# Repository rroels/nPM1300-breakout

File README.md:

# Nordic nPM1300 Breakout Board

> [!WARNING]
> The information and material (code, designs, files, ...) are provided "AS IS". We make no representation or warranty of any kind, express or implied, regarding the accuracy, adequacy, validity, reliability, availability, or completeness of any information or material. Use this at your own risk.

> [!WARNING]
> At the time of writing this PCB has not even been produced yet, and as such, it has not even been tested yet! Once it has been properly tested, I will confirm that everything works as expected.

## Introduction

This is a breakout board for the Nordic nPM1300 Power Management IC.

[https://www.nordicsemi.com/Products/nPM1300](https://www.nordicsemi.com/Products/nPM1300)

## Change Log

* v1.0
  * Initial design 

## Design Considerations

In this design, the nPM1300 is configured like this:

* BUCK1 disabled
* BUCK2 enabled, for converting battery or USB input to 3.3V
* 2 load switches at 3.3V (LS1 and LS2)
* no LDO 
* 3 LEDs
* I2C interface

## Schematics 

## How to Obtain the Physical PCB

The Gerber file is in this repository (`kicad/gerbers/nPM1300-breakout.zip`). Simply upload this file a PCB manufacturer of your choice (JLPCB, PCBWay, ...), and you they will make it for you for as low as \$5 for 5 pieces (with the cheapest shipping option, which can take a few weeks).

For JLCPCB, select the order number option where they will replace "JLCJLCJLCJLC" on the board with the actual order number.

> [!WARNING]
> Note that will still have to solder the components onto the PCB yourself!

## How to Edit Design

Everything you need to edit this design in KiCad 8 is included in the repository.

However, this project uses symbols, footprints and 3D models from [Component Search Engine](https://componentsearchengine.com/). Their license allows us to do pretty much whatever we want with them, except redistributing them. For this reason I can't include them in this repository.

If you would like to edit the design yourself, you will need to download the following component libraries from [https://componentsearchengine.com/](https://componentsearchengine.com/) (it's free!):

* [https://componentsearchengine.com/part-view/NPM1300-QEAA-R/Nordic%20Semiconductor](https://componentsearchengine.com/part-view/NPM1300-QEAA-R/Nordic%20Semiconductor)
* [https://componentsearchengine.com/part-view/53261-0271/Molex](https://componentsearchengine.com/part-view/53261-0271/Molex)

You will also need this from SnapEDA:

* [https://www.snapeda.com/parts/21296912/TE%20Connectivity/view-part/?ref=te_in&t=USB4105-GF-A&con_ref=None](https://www.snapeda.com/parts/21296912/TE%20Connectivity/view-part/?ref=te_in&t=USB4105-GF-A&con_ref=None)

From the downloaded zip files, move the content of the `KiCad` and `3D` subfolders into the project structure, so that the end-result looks like this:

The KiCad project is configured to look for these files in these locations, using relative paths, so no changes to the project itself are required.	

## Sources

* [https://www.nordicsemi.com/Products/nPM1300](https://www.nordicsemi.com/Products/nPM1300)
* [https://docs.nordicsemi.com/category/npm1300-category](https://docs.nordicsemi.com/category/npm1300-category)

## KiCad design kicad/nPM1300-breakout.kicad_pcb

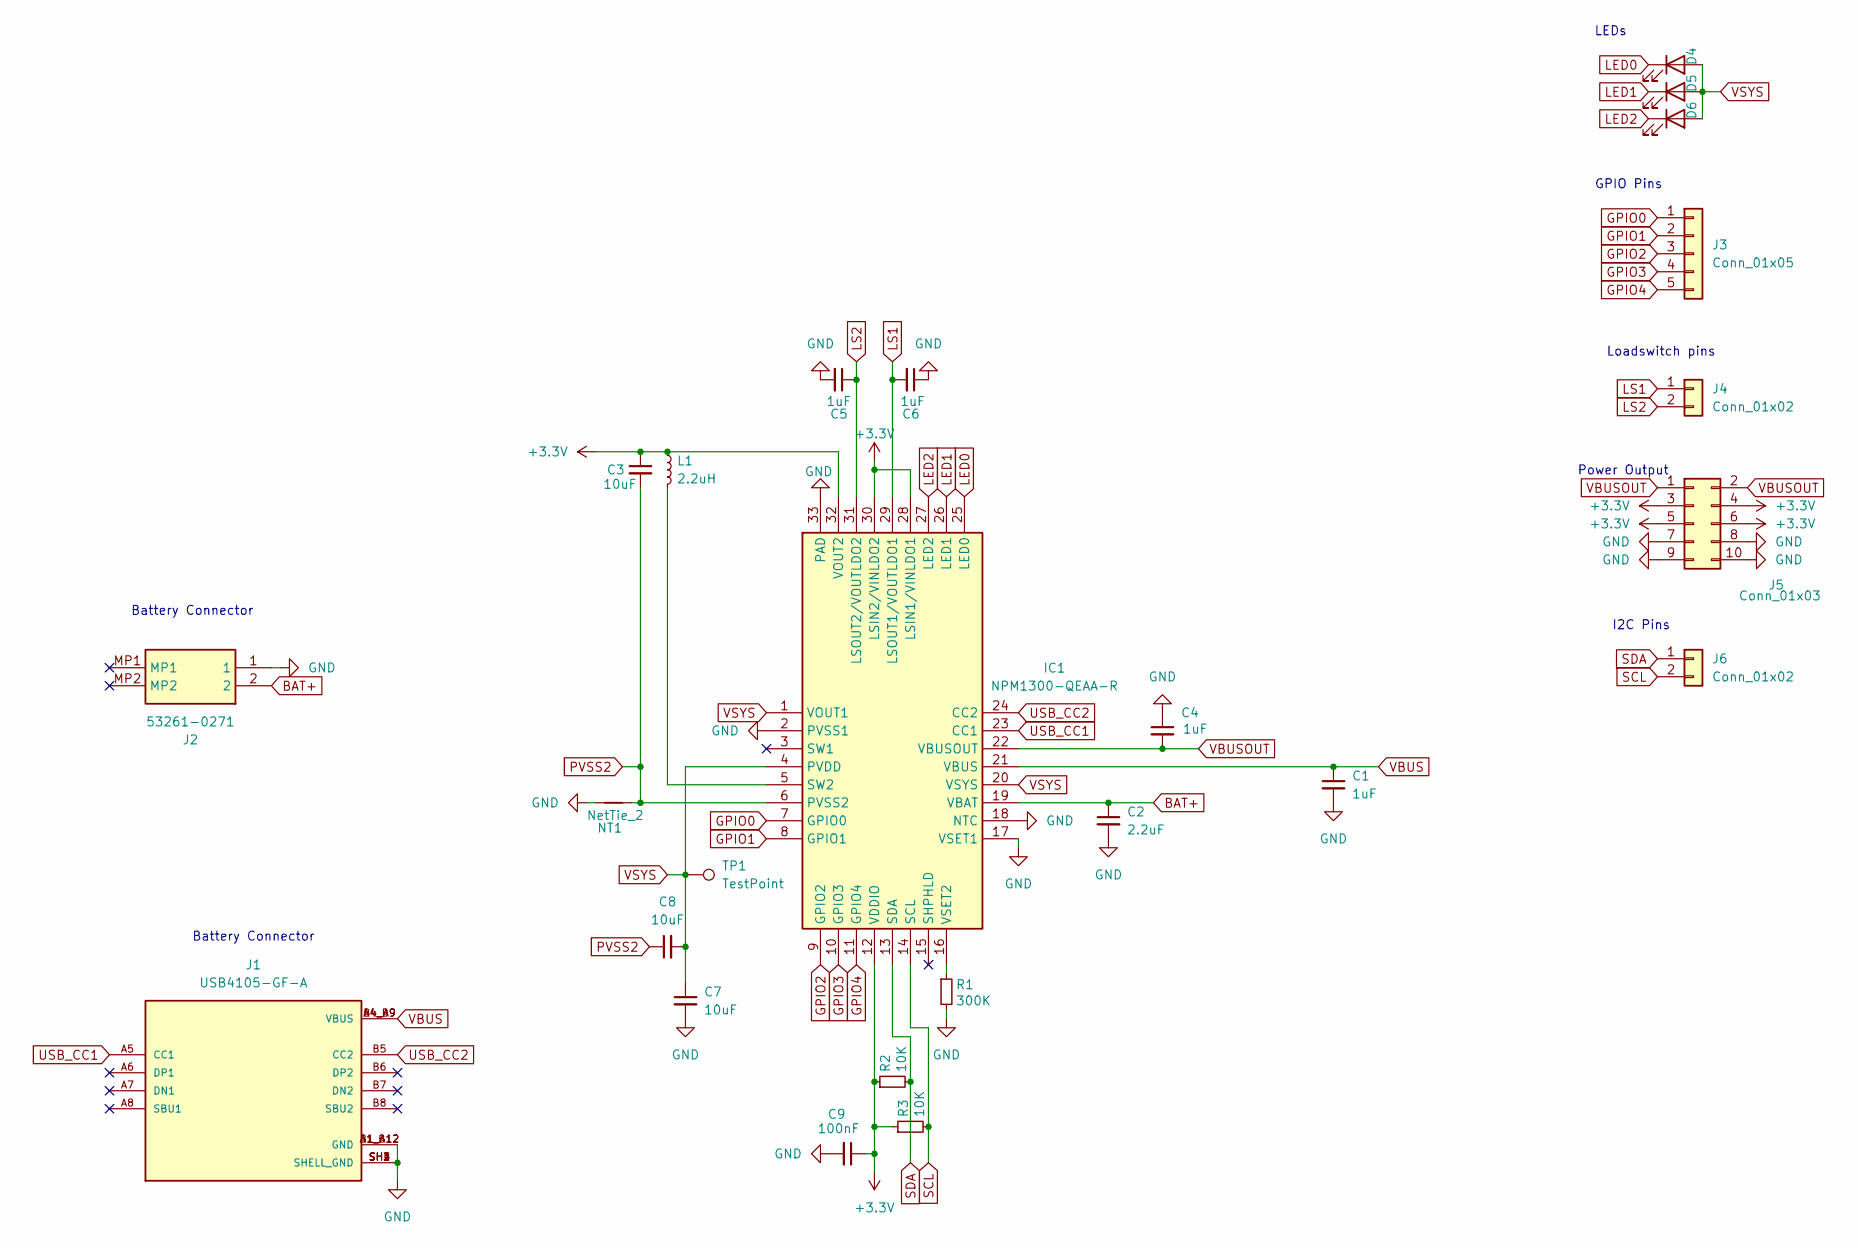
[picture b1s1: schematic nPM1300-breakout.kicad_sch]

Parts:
C1, C4, C5, C6: 1uF; C_0603_1608Metric_Pad1.08x0.95mm_HandSolder
C2: 2.2uF; C_0603_1608Metric_Pad1.08x0.95mm_HandSolder
C3, C7, C8: 10uF; C_0603_1608Metric_Pad1.08x0.95mm_HandSolder
C9: 100nF; C_0603_1608Metric_Pad1.08x0.95mm_HandSolder
D4, D5, D6: LED; LED_0603_1608Metric_Pad1.05x0.95mm_HandSolder
IC1: NPM1300-QEAA-R; QFN50P500X500X90-33N; Manufacturer_Part_Number NPM1300-QEAA-R; Mouser Part Number 949-NPM1300-QEAA-R
J1: USB4105-GF-A; GCT_USB4105-GF-A; PARTREV B4
J2: 53261-0271; 532610271; Manufacturer_Part_Number 53261-0271; Mouser Part Number 538-53261-0271
J3: Conn_01x05; PinHeader_1x05_P2.54mm_Vertical
J4, J6: Conn_01x02; PinHeader_1x02_P2.54mm_Vertical
J5: Conn_01x03; PinHeader_2x05_P2.54mm_Vertical
L1: 2.2uH; L_0805_2012Metric_Pad1.05x1.20mm_HandSolder
NT1: NetTie_2; NetTie-2_SMD_Pad0.5mm
R1: 300K; R_0603_1608Metric_Pad0.98x0.95mm_HandSolder
R2, R3: 10K; R_0603_1608Metric_Pad0.98x0.95mm_HandSolder
TP1: TestPoint; TestPoint_Pad_D1.0mm

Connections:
+3.3V: C3.1, C9.1, IC1.12 (VDDIO), IC1.28 (LSIN1/VINLDO1), IC1.30 (LSIN2/VINLDO2), IC1.32 (VOUT2), J5.3, J5.4, J5.5, J5.6, L1.1, R2.1, R3.1
BAT+: C2.1, IC1.19 (VBAT), J2.2
GND: C1.2, C2.2, C4.1, C5.2, C6.1, C7.2, C9.2, IC1.2 (PVSS1), IC1.17 (VSET1), IC1.18 (NTC), IC1.33 (PAD), J1.A1_B12 (GND), J1.B1_A12 (GND), J1.SH1 (SHELL_GND), J1.SH2 (SHELL_GND), J1.SH3 (SHELL_GND), J1.SH4 (SHELL_GND), J2.1, J5.7, J5.8, J5.9, J5.10, NT1.1, R1.2
GPIO0: IC1.7 (GPIO0), J3.1
GPIO1: IC1.8 (GPIO1), J3.2
GPIO2: IC1.9 (GPIO2), J3.3
GPIO3: IC1.10 (GPIO3), J3.4
GPIO4: IC1.11 (GPIO4), J3.5
LED0: D4.1 (K), IC1.25 (LED0)
LED1: D5.1 (K), IC1.26 (LED1)
LED2: D6.1 (K), IC1.27 (LED2)
LS1: C6.2, IC1.29 (LSOUT1/VOUTLDO1), J4.1
LS2: C5.1, IC1.31 (LSOUT2/VOUTLDO2), J4.2
unnamed: IC1.5 (SW2), L1.2
unnamed: IC1.16 (VSET2), R1.1
PVSS2: C3.2, C8.1, IC1.6 (PVSS2), NT1.2
SCL: IC1.14 (SCL), J6.2, R3.2
SDA: IC1.13 (SDA), J6.1, R2.2
USB_CC1: IC1.23 (CC1), J1.A5 (CC1)
USB_CC2: IC1.24 (CC2), J1.B5 (CC2)
VBUS: C1.1, IC1.21 (VBUS), J1.A4_B9 (VBUS), J1.B4_A9 (VBUS)
VBUSOUT: C4.2, IC1.22 (VBUSOUT), J5.1, J5.2
VSYS: C7.1, C8.2, D4.2 (A), D5.2 (A), D6.2 (A), IC1.1 (VOUT1), IC1.4 (PVDD), IC1.20 (VSYS), TP1.1; also elsewhere on the board

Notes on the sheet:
Battery Connector
GPIO Pins
Power Output
LEDs
I2C Pins
Loadswitch pins

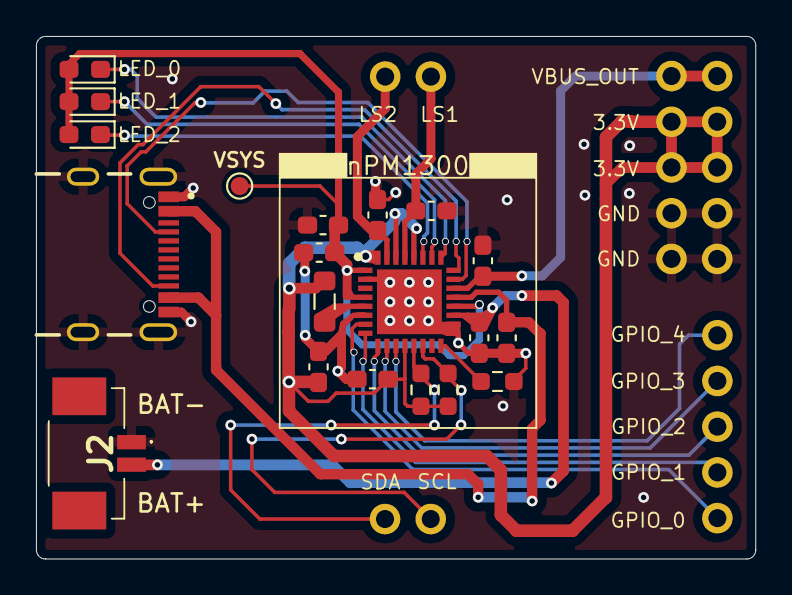
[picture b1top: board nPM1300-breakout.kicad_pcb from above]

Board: 2 copper layers, 40.0 x 29.0 mm, 25 parts (0 on the bottom side), 23 nets.

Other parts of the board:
VSYS: TestPoint; TestPoint_Pad_D1.0mm

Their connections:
VSYS: VSYS.1; also elsewhere on the board
